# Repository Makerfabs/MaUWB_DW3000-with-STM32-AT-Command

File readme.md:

# MaUWB_DW3000 with STM32 AT Command

```

Version:    V1.3
Author:     Vincent
Create Date:    2023/10/14
Note:

    2023/10/19 V1.1: Add at command usage and hardware.
    2023/12/11 V1.2: Add a packaged position.py.
    2024/9/24  V1.3: MaUWB(v1.1.1).HEX is released to support simultaneous data transmission for ranging.

```

[toc]

# Makerfabs

[Makerfabs home page](https://www.makerfabs.com/)

[Makerfabs Wiki](https://wiki.makerfabs.com/)

# MaUWB_DW3000 with STM32 AT Command
## Intruduce

Product Link ：[MaUWB_DW3000 with STM32 AT Command](https://www.makerfabs.com/mauwb-dw3000-with-stm32-at-command.html) 

Wiki Link : [MaUWB_DW3000 with STM32 AT Command](https://wiki.makerfabs.com/%20MaUWB_DW3000-with-STM32-AT-Command.html)

The latest UWB module that solves multiple anchors& tags mutual conflicts, support max 8 Anchors + 64 tags in application, to create a multi-anchor multi-tag positioning system, and add the ability to set the Anchor antenna delay

## Feature

- DW3000 with PA, max range 500M
- Precision 0.5M(in range 100m)
- Support 8 anchors+ 64 Tags application
- Distance measurement and data transmission.

# Code

## AT Command Usage

Please refer to the AT Command manual for detailed use.

hardware\Makerfabs UWB AT Module AT Command Manual(v1.0.5).pdf

### Initial configuration

You are advised to use serial_test.ino to configure the UWB AT module.
Each time you configure the UWB AT module, follow the following configuration sequence:

```C 

AT?

//Test whether the serial port communication is normal

AT+RESTORE

//Restore factory Settings

AT+SETCFG=(x1),(x2),(x3),(x4)
// Such as: AT+SETCFG=0,1,0,1

//Set the role and frequency
//More on that later

AT+SETCAP=10,15,0

//Set the capacity and send time slot

AT+SETRPT=1

// Turn on automatic reporting

AT+SAVE

// Save

AT+RESTART

// Restart

```

### Set the role and frequency

AT+SETCFG=(x1),(x2),(x3),(x4)

Parameter description

x1: Device ID(Note: Base station 0-7, label 0-31)

x2: Device role (0: tag /1: base station)

x3: device air speed (0:850K/1:6.8M, default :6.8M)

x4: Range filtering enabled (0: off /1: on)

Generally, 850K is used and distance filtering is turned on.

```c
//Example
//A0
AT+SETCFG=0,1,0,1

//A1
AT+SETCFG=1,1,0,1

//A2
AT+SETCFG=2,1,0,1

//A3
AT+SETCFG=3,1,0,1

//T0
AT+SETCFG=0,0,0,1

//T1
AT+SETCFG=1,0,0,1

//T2
AT+SETCFG=2,0,0,1

//T3
AT+SETCFG=3,0,0,1

//T4
AT+SETCFG=4,0,0,1

//T5
AT+SETCFG=5,0,0,1

```

### Set data transmit mode

AT+SETCAP=(x1),(x2),(x3)

x1:Tag capacity (default: 10, maximum: 64)

x2:Time of a single time slot

X3:extMode (0: normal packet when communicating, 1: extended packet when communicating)

6.8M, Minimum single slot time 10ms for normal packet, Minimumsingle slot time 10ms for extended packet. 

850K. Minimum single slot time 15ms for normal packet, Minimumsingle slot time 25ms for extended packet.

```c
// 850K
AT+SETCAP=10,25,1

// 6.8M
AT+SETCAP=10,10,1

```

### Send data

Must set data transmit mode first.

AT+DATA=(x1),(x2)

x1:Length of transmitted data

x2:Transmitted data

```c

AT+DATA=32,HELLO_WORLD_123456

```

## Compiler Options

- Use type-c use cable connect USB-TTL to PC.
- Select "ESP32 DEV Module"

Libraries:
- Use 2.0.0   Wire
- Use 1.11.7   Adafruit_GFX_Library
- Use 1.14.4   Adafruit_BusIO
- Use 2.0.0   SPI
- Use 2.5.7   Adafruit_SSD1306

## Example

### esp32_at_t0

Factory firmware, reset the UWB AT module and set it to Tag 0.

### esp32_at_t0

Reset the UWB AT module and set it to Anchor 0.

### serial_test

Serial port test

### data_transmit

This command is used to test the newly added AT+DATA command, which can transmit data.

### Indoor positioning

Simple indoor positioning example, using json to pass data.
You need to configure all UWB modules in advance and burn the get_range program to A0.
This program parses the AT instructions into JSON format and uploads them through the serial port.

The corresponding Python packages, such as PySerial and PyGame, need to be installed in advance.
And modify the position of several origin points in the code:

(unit cm)
```Python

A0X, A0Y = 300, 200
A1X, A1Y = 300, 300
A2X, A2Y = 0, 0
A3X, A3Y = 0, 700

```
Connect the PC with a USB cable and run the Python program.

**This code is for promotional use only and is not part of the UWB AT module product, and Makerfabs does not provide further technical support.**

**Update**

For a more convenient experience for some customers, we provide a packaged exe file. Please insert A0 configured first, and be sure to burn the get_range program.

And make sure the computer's serial port is not connected to any other devices, because this program is scanning the first COM device.

And this program has been determined to be in the range of 10 meters by 10 meters, and will be accompanied by various crashes.

We are not responsible for any technical support for this software, for reference only, only for the packaging of position.py.

# AT Module Firmware Update

Connect ST-Link to PC.

Open STM32 ST-LINK Utility.

Open "Target/Settings", it should display ST-Link Serial Number.

Close the window, back to main page.

Connect ST-Link and MaUWB.

And use TypeC cable power on MaUWB, the power of ST-Link is not enough.

Like this:

|ST-LINK|3v3|gnd|clk|dio|
|----|----|----|----|----|
|UWB_AT|3.3v|gnd|swclk|swdio|

Click "connect to target", it should be display device type. And click "Program verify".

Select hex file, click "START" to download.

# STM32 Pin Map

STM32F103RCT6

|Index|STM32|PINOUT|Function|
|----|----|----|----|
|1|PA0|DW_RSTn|Reset pin. Active Low Output.|
|2|PA4|DW_CSn|SPI chip select|
|3|PA5|DW_SLK|SPI clock|
|4|PA6|DW_MISO|SPI data output|
|5|PA7|DW_MOSI|SPI data input.|
|6|PA8|DW_EXTON|External device enable. Asserted during wake up process and held active until device enters sleep mode. Can be used to control external DC-DC converters or other circuits that are not required when the device is in sleep mode so as to minimize power consumption.|
|7|PB0|DW_wakeup|When asserted into its active high state, the WAKEUP pin brings the DW3000 out of SLEEP or DEEPSLEEP states into operational mode|
|8|PB5|DW_IRQn|Interrupt Request output from the DW3000 to the host processor. By default IRQ is an active-high output but may be configured to be active low if required. For correct operation in SLEEP and DEEPSLEEP modes it should be configured for active high operation. This pin will float in SLEEP and DEEPSLEEP states and may cause spurious interrupts unless pulled low. When the IRQ functionality is not being used the pin may be reconfigured as a general purpose I/O line, GPIO8.|
|10|PA1|LED_RUN|Indicator output pin|
|11|PA9|USART1_TX|
|12|PA10|USART1_RX|
|13|PA13|SWDIO|
|14|PA14|SWCLK|

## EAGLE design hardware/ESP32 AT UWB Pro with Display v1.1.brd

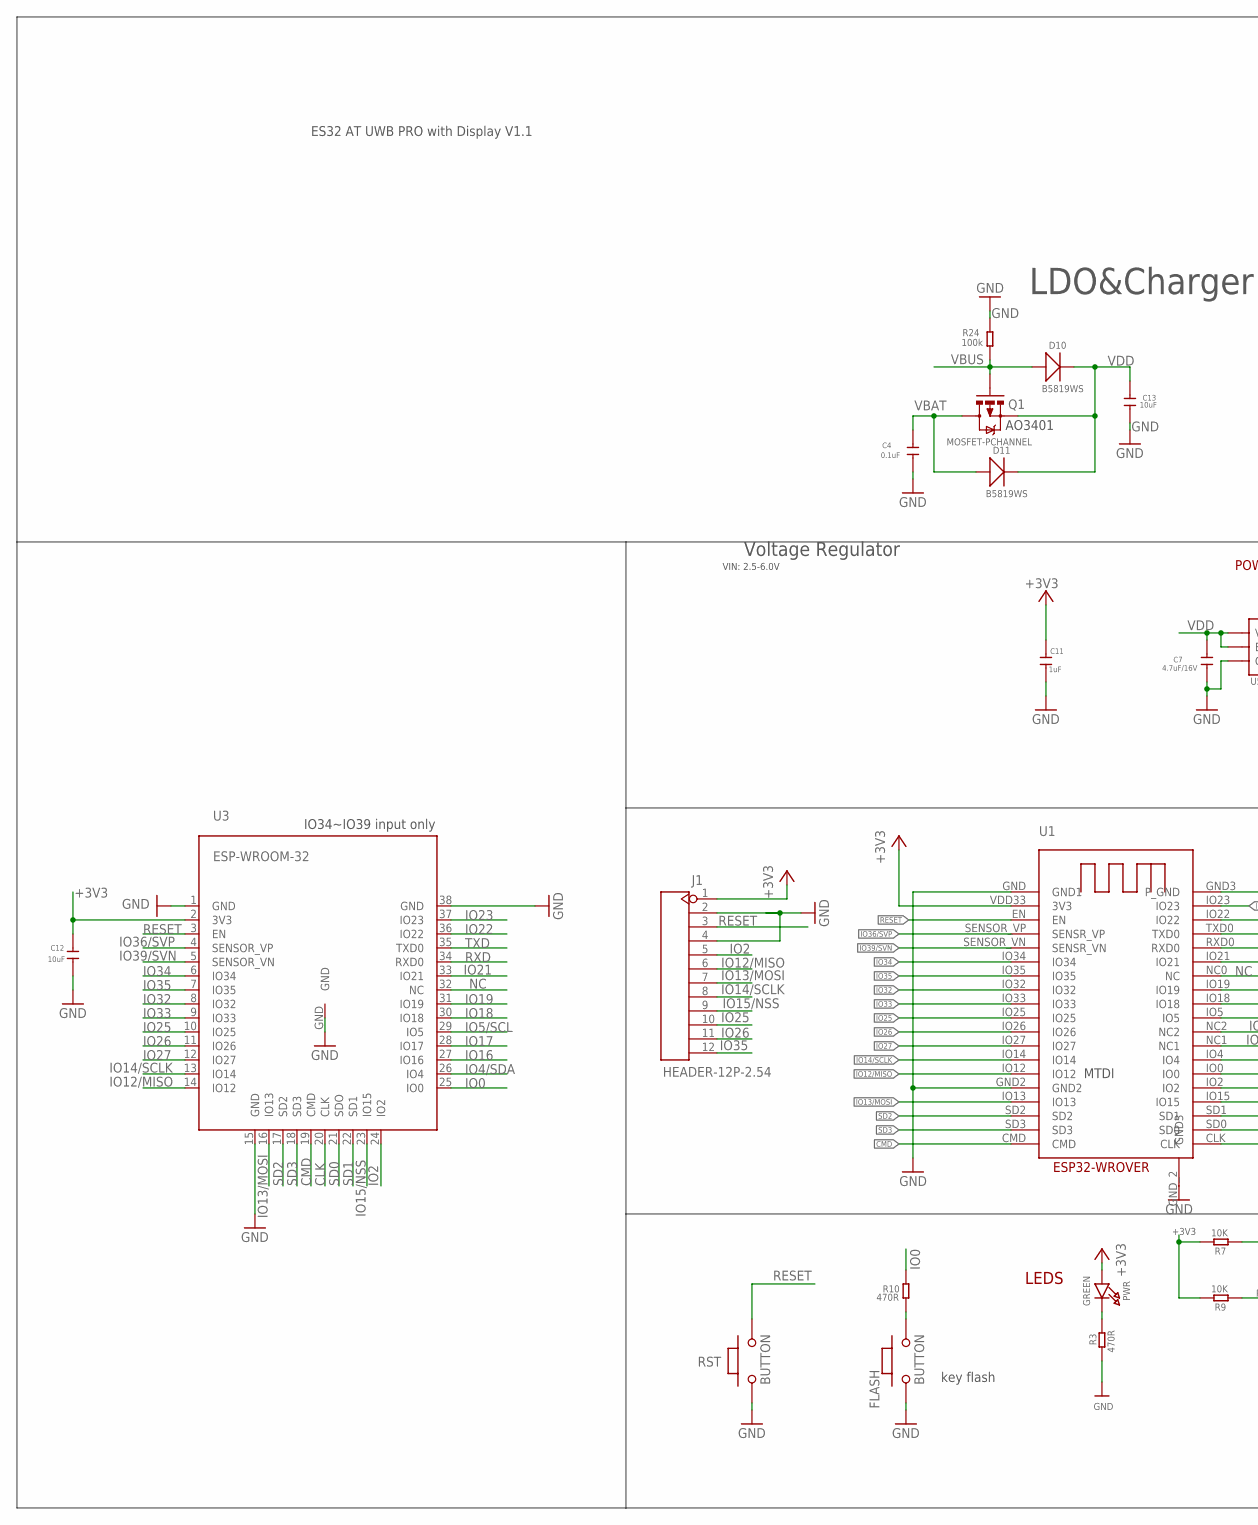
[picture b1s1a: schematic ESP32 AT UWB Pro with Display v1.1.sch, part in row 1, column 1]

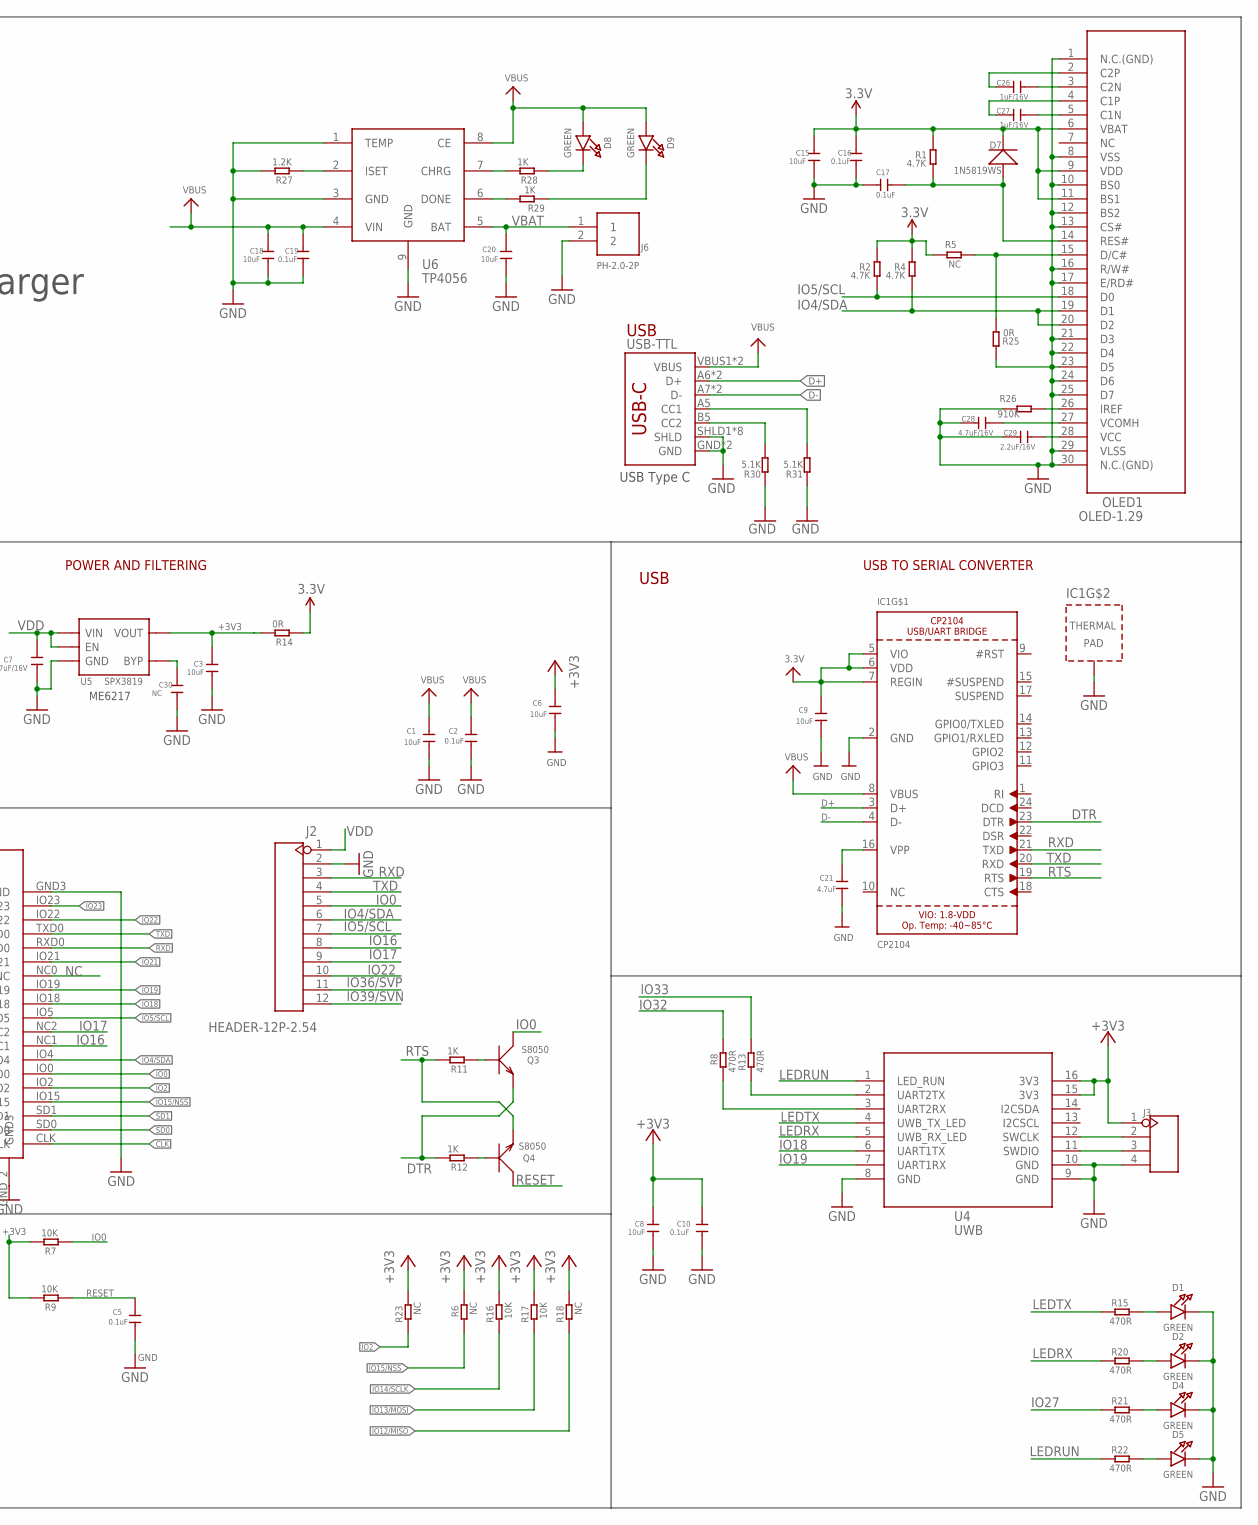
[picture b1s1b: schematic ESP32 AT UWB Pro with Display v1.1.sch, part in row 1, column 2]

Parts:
C1, C3, C6, C8, C9, C12, C13, C15, C18, C20: 10uF; 0603
C2, C4, C5, C10, C16, C17, C19: 0.1uF; 0603
C7, C28: 4.7uF/16V; 0603
C11: 1uF; 0603
C21: 4.7uF; 0603
C26, C27: 1uF/16V; 0603
C29: 2.2uF/16V; 0603
C30: NC; 0603
D1, D2, D4, D5, D8, D9: GREEN; CHIPLED_0805_NOOUTLINE
D7: 1N5819WS; SOD323
D10, D11: B5819WS; SOD323
FLASH: BUTTON; 157SW
IC1: CP2104; QFN24_4MM_SMSC
J1, J2: HEADER-12P-2.54; 12P-2.54
J3: HEADER-4P-60/35MILROUND; 4P-65/35ROUND
J6: PH-2.0-2P
OLED1: OLED-1.29
PWR: GREEN; CHIPLED_0805_NOOUTLINE
Q1: MOSFET-PCHANNEL; SOT23-3
Q3, Q4: S8050; SOT23
R1, R2, R4: 4.7K; R0603
R3, R8, R10, R13, R15, R20, R21, R22: 470R; R0603
R5, R6, R18, R23: NC; R0603
R7, R9, R16, R17: 10K; R0603
R11, R12, R28, R29: 1K; R0603
R14, R25: 0R; R0603
R24: 100k; R0603
R26: 910K; R0603
R27: 1.2K; R0603
R30, R31: 5.1K; DISCRETE_R0603
RST: BUTTON; 157SW
U1: ESP32-WROVER
U3: ESP-WROOM-32
U4: UWB
U5: SPX3819; SOT23-5
U6: TP4056; SOP8-1.27P
USB-TTL: USB_C5; USB-C-16P-5

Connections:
3.3V: C15.1, C16.1, D7.-, OLED1.6 (VBAT), OLED1.9 (VDD), OLED1.11 (BS1), R1.2, R2.2, R4.2, R5.2, R14.1
+3V3: C3.1, C6.1, C8.1, C9.1, C10.1, C11.1, C12.1, IC1.5 (VIO), IC1.6 (VDD), IC1.7 (REGIN), J1.1, J3.1, PWR.A, R6.2, R7.2, R9.2, R14.2, R16.2, R17.2, R18.2, R23.2, U1.VDD33 (3V3), U3.2 (3V3), U4.15 (3V3), U4.16 (3V3), U5.5 (VOUT)
CLK: U1.CLK, U3.20 (CLK)
CMD: U1.CMD, U3.19 (CMD)
D+: IC1.3 (D+), USB-TTL.A6 (D+), USB-TTL.B6 (D+)
D-: IC1.4 (D-), USB-TTL.A7 (D-), USB-TTL.B7 (D-)
DTR: IC1.23 (DTR), Q3.2 (E), R12.2
GND: C1.2, C2.2, C3.2, C4.2, C5.2, C6.2, C7.2, C8.2, C9.2, C10.2, C11.2, C12.2, C13.1, C15.2, C16.2, C17.1, C18.2, C19.2, C20.2, C21.2, C28.1, C29.1, C30.2, D1.C, D2.C, D4.C, D5.C, FLASH.1, IC1.2 (GND), IC1.THERM (TP), J1.2, J1.4, J2.2, J3.4, J6.2, OLED1.1 (N.C.(GND)), OLED1.8 (VSS), OLED1.10 (BS0), OLED1.12 (BS2), OLED1.13 (CS#), OLED1.16 (R/W#), OLED1.17 (E/RD#), OLED1.21 (D3), OLED1.22 (D4), OLED1.23 (D5), OLED1.24 (D6), OLED1.25 (D7), OLED1.29 (VLSS), OLED1.30 (N.C.(GND)), R3.1, R24.2, R25.2, R26.2, R27.2, R30.1, R31.1, RST.1, U1.GND (GND1), U1.GND2, U1.GND3 (P_GND), U1.GND_2 (GND3), U3.1 (GND), U3.15 (GND), U3.38 (GND), U3.GND, U4.8 (GND), U4.9 (GND), U4.10 (GND), U5.2 (GND), U6.1 (TEMP), U6.3 (GND), U6.9 (GND), USB-TTL.GND, USB-TTL.GND2 (GND), USB-TTL.SHLD1 (SHLD), USB-TTL.SHLD2 (SHLD), USB-TTL.SHLD3 (SHLD), USB-TTL.SHLD4 (SHLD), USB-TTL.SHLD5 (SHLD), USB-TTL.SHLD6 (SHLD), USB-TTL.SHLD7 (SHLD), USB-TTL.SHLD8 (SHLD)
IO0: J2.5, Q3.3 (C), R7.1, R10.2, U1.IO0, U3.25 (IO0)
IO2: J1.5, R23.1, U1.IO2, U3.24 (IO2)
IO4/SDA: J2.6, OLED1.19 (D1), OLED1.20 (D2), R4.1, U1.IO4, U3.26 (IO4)
IO5/SCL: J2.7, OLED1.18 (D0), R2.1, U1.IO5, U3.29 (IO5)
IO12/MISO: J1.6, R18.1, U1.IO12, U3.14 (IO12)
IO13/MOSI: J1.7, R17.1, U1.IO13, U3.16 (IO13)
IO14/SCLK: J1.8, R16.1, U1.IO14, U3.13 (IO14)
IO15/NSS: J1.9, R6.1, U1.IO15, U3.23 (IO15)
IO16: J2.8, U1.NC1, U3.27 (IO16)
IO17: J2.9, U1.NC2, U3.28 (IO17)
IO18: U1.IO18, U3.30 (IO18), U4.6 (UART1TX)
IO19: U1.IO19, U3.31 (IO19), U4.7 (UART1RX)
IO21: U1.IO21, U3.33 (IO21)
IO22: J2.10, U1.IO22, U3.36 (IO22)
IO23: U1.IO23, U3.37 (IO23)
IO25: J1.10, U1.IO25, U3.10 (IO25)
IO26: J1.11, U1.IO26, U3.11 (IO26)
IO27: R21.1, U1.IO27, U3.12 (IO27)
IO32: R8.2, U1.IO32, U3.8 (IO32)
IO33: R13.2, U1.IO33, U3.9 (IO33)
IO34: U1.IO34, U3.6 (IO34)
IO35: J1.12, U1.IO35, U3.7 (IO35)
IO36/SVP: J2.11, U1.SENSOR_VP (SENSR_VP), U3.4 (SENSOR_VP)
IO39/SVN: J2.12, U1.SENSOR_VN (SENSR_VN), U3.5 (SENSOR_VN)
LEDRUN: R22.1, U4.1 (LED_RUN)
LEDRX: R20.1, U4.5 (UWB_RX_LED)
LEDTX: R15.1, U4.4 (UWB_TX_LED)
unnamed: D1.A, R15.2
unnamed: C21.1, IC1.16 (VPP)
unnamed: C17.2, D7.+, OLED1.14 (RES#), R1.1
unnamed: OLED1.15 (D/C#), R5.1, R25.1
unnamed: PWR.C, R3.2
unnamed: C28.2, OLED1.27 (VCOMH)
unnamed: C26.2, OLED1.3 (C2N)
unnamed: C29.2, OLED1.28 (VCC)
unnamed: OLED1.26 (IREF), R26.1
unnamed: R13.1, U4.2 (UART2TX)
unnamed: R8.1, U4.3 (UART2RX)
unnamed: Q4.1 (B), R12.1
unnamed: Q3.1 (B), R11.1
unnamed: FLASH.2, R10.1
unnamed: D2.A, R20.2
unnamed: D4.A, R21.2
unnamed: D5.A, R22.2
unnamed: C26.1, OLED1.2 (C2P)
unnamed: C27.1, OLED1.4 (C1P)
unnamed: C27.2, OLED1.5 (C1N)
unnamed: R27.1, U6.2 (ISET)
unnamed: R31.2, USB-TTL.A5 (CC1)
unnamed: R30.2, USB-TTL.B5 (CC2)
unnamed: J3.3, U4.11 (SWDIO)
unnamed: J3.2, U4.12 (SWCLK)
unnamed: R28.2, U6.7 (CHRG)
unnamed: R29.2, U6.6 (DONE)
unnamed: D8.C, R28.1
unnamed: D9.C, R29.1
unnamed: C30.1, U5.4 (BYP)
NC: U1.NC0 (NC), U3.32 (NC)
RESET: C5.1, J1.3, Q4.3 (C), R9.1, RST.2, U1.EN, U3.3 (EN)
RTS: IC1.19 (RTS), Q4.2 (E), R11.2
RXD: IC1.21 (TXD), J2.3, U1.RXD0, U3.34 (RXD0)
SD0: U1.SD0, U3.21 (SDO)
SD1: U1.SD1, U3.22 (SD1)
SD2: U1.SD2, U3.17 (SD2)
SD3: U1.SD3, U3.18 (SD3)
TXD: IC1.20 (RXD), J2.4, U1.TXD0, U3.35 (TXD0)
VBAT: C4.1, C20.1, D11.+, J6.1, Q1.3 (D), U6.5 (BAT)
VBUS: C1.1, C2.1, C18.1, C19.1, D8.A, D9.A, D10.+, IC1.8 (VBUS), Q1.1 (G), R24.1, U6.4 (VIN), U6.8 (CE), USB-TTL.VBUS1 (VBUS), USB-TTL.VBUS2 (VBUS)
VDD: C7.1, C13.2, D10.-, D11.-, J2.1, Q1.2 (S), U5.1 (VIN), U5.3 (EN)

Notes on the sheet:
USB
LEDS
POWER AND FILTERING
USB TO SERIAL CONVERTER
key flash
ES32 AT UWB PRO with Display V1.1
MTDI
IO34~IO39 input only
Voltage Regulator
VIN: 2.5-6.0V
USB Type C
LDO&Charger
AO3401
ME6217

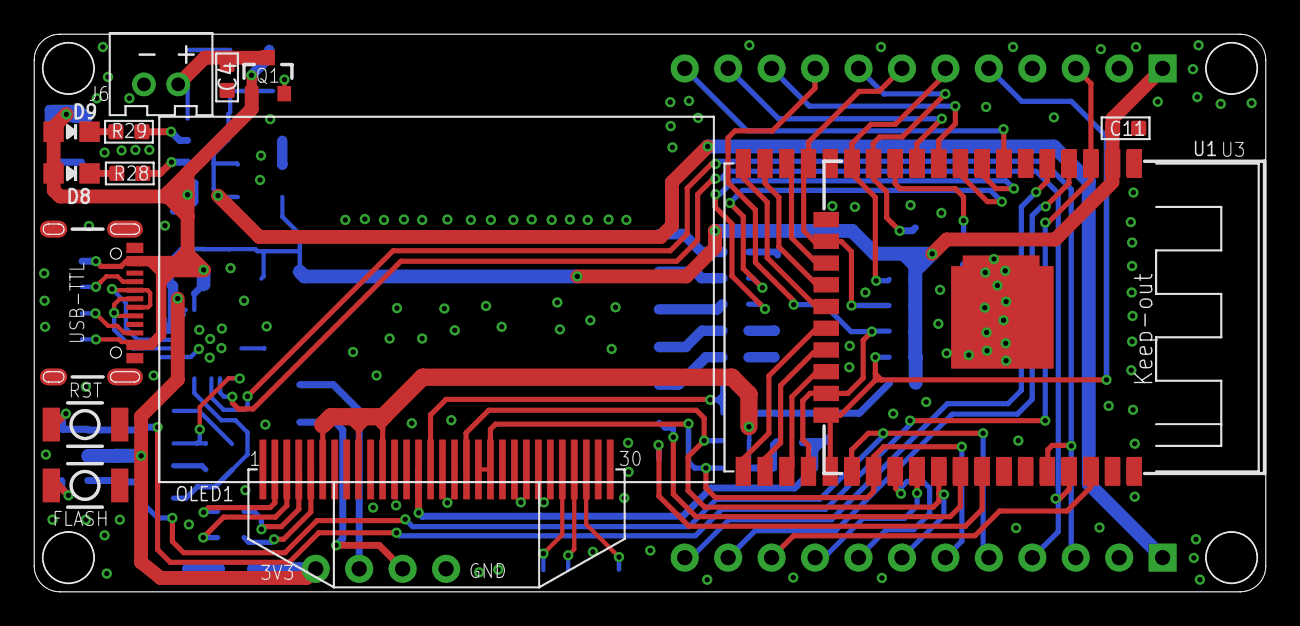
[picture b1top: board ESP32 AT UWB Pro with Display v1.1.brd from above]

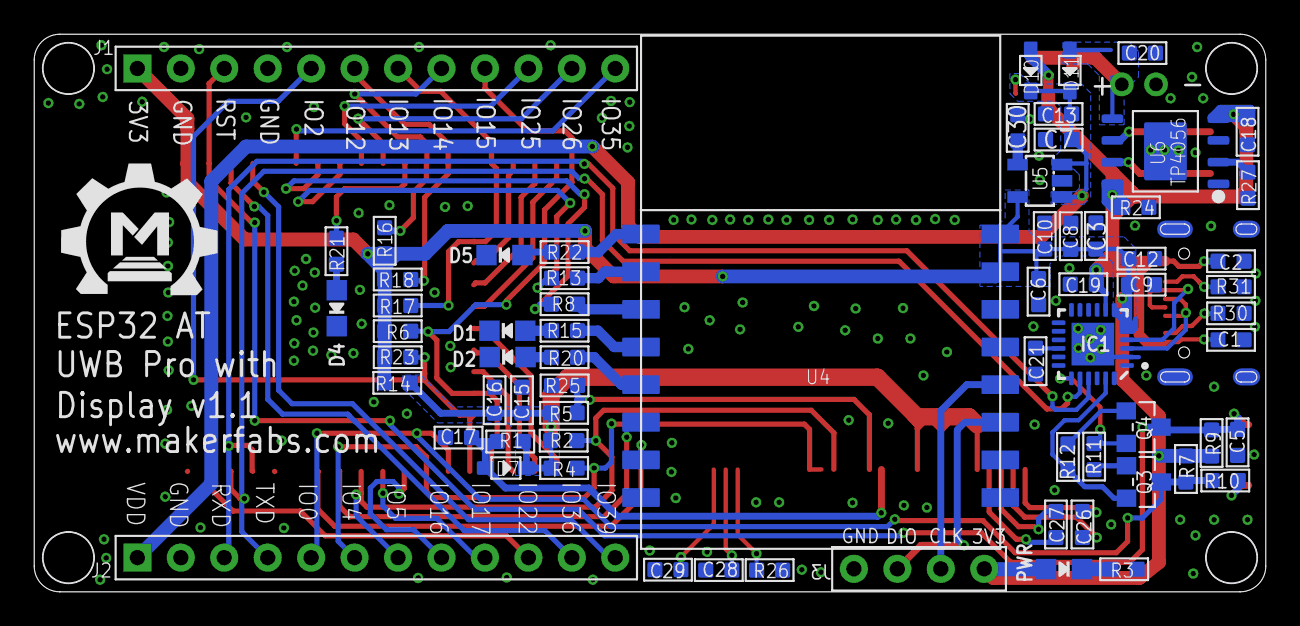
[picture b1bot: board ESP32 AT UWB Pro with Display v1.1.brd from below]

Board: 2 copper layers, 72.0 x 32.6 mm, 83 parts (69 on the bottom side), 77 nets.

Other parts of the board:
U$1: MAKERFABS_0.3

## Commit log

2023-10-13 Create project
2023-10-14 Edit readme
2023-10-19 Add hardware and at command usage
2023-11-02 Add at firmware update
2023-11-20 Optimized code
2023-12-11 V1.2
2024-06-02 added support for ESP32-S3
2024-09-20 Add data transform demo
2024-09-20 Update manual
2025-02-27 Update
    添加两条新AT指令

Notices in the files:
parts and their libraries:
microbuilder: This work is placed in the public domain, and may be freely used for commercial and non-commercial work with the following conditions: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
User-Submitted: Licensing: Creative Commons ShareAlike 4.0 International - https://creativecommons.org/licenses/by-sa/4.0
